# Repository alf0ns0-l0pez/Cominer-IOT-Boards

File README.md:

# Cominer-IOT-Boards
Cominer IOT Boards - IOT Multiple Actions

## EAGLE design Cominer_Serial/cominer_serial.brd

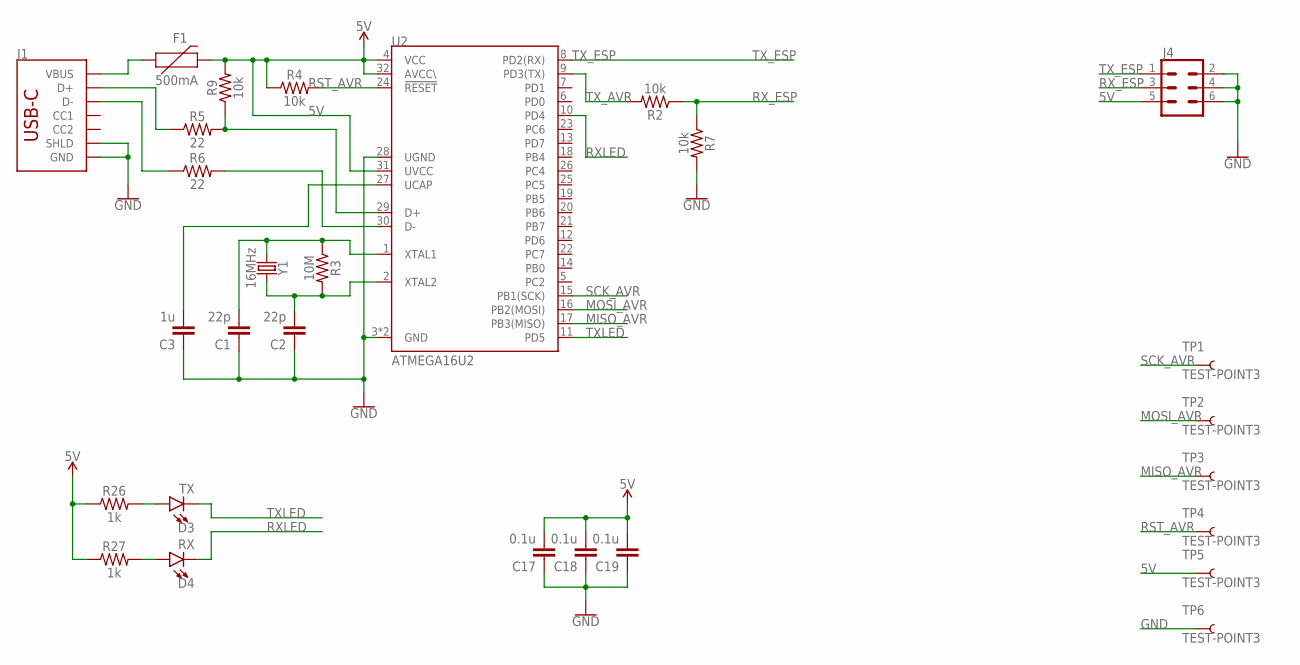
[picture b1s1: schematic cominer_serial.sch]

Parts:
C1, C2: 22p; 0805
C3: 1u; 0805
C17, C18, C19: 0.1u; 0805
D3: TX; LED-0603
D4: RX; LED-0603
F1: 500mA; 1812
J1: USB_C; USB-C-16P-SMD
J4: CONN_03X2SHROUD; 2X3-SHROUDED
R2, R4, R7, R9: 10k; 0805
R3: 10M; 0805
R5, R6: 22; 0805
R26, R27: 1k; 0805
TP1, TP2, TP3, TP4, TP5, TP6: TEST-POINT3; PAD.03X.03
U2: ATMEGA16U2; QFN32
Y1: 16MHz; CRYSTAL-SMD-5X3.2-4PAD

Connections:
5V: C17.2, C18.2, C19.2, F1.2, J4.5, R4.1, R9.2, R26.1, R27.1, TP5.P$1, U2.4 (VCC), U2.31 (UVCC), U2.32 (AVCC\)
GND: C1.1, C2.1, C3.1, C17.1, C18.1, C19.1, J1.GND, J1.GND2 (GND), J1.SHLD1 (SHLD), J1.SHLD2 (SHLD), J1.SHLD3 (SHLD), J1.SHLD4 (SHLD), J4.2, J4.4, J4.6, R7.2, TP6.P$1, U2.3 (GND), U2.28 (UGND), U2.EP (GND)
MISO_AVR: TP3.P$1, U2.17 (PB3(MISO))
MOSI_AVR: TP2.P$1, U2.16 (PB2(MOSI))
unnamed: C1.2, R3.1, U2.1 (XTAL1), Y1.1
unnamed: C2.2, R3.2, U2.2 (XTAL2), Y1.3 (2)
unnamed: C3.2, U2.27 (UCAP)
unnamed: R6.2, U2.30 (D-)
unnamed: R5.2, R9.1, U2.29 (D+)
unnamed: J1.A6 (D+), J1.B6 (D+), R5.1
unnamed: J1.A7 (D-), J1.B7 (D-), R6.1
unnamed: F1.1, J1.VBUS1 (VBUS), J1.VBUS2 (VBUS)
unnamed: D3.A, R26.2
unnamed: D4.A, R27.2
RST_AVR: R4.2, TP4.P$1, U2.24 (!RESET)
RXLED: D4.C, U2.10 (PD4)
RX_ESP: J4.3, R2.1, R7.1
SCK_AVR: TP1.P$1, U2.15 (PB1(SCK))
TXLED: D3.C, U2.11 (PD5)
TX_AVR: R2.2, U2.9 (PD3(TX))
TX_ESP: J4.1, U2.8 (PD2(RX))

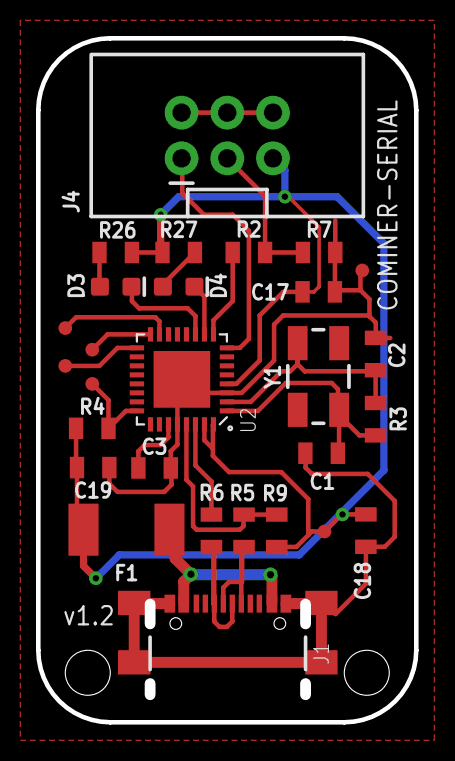
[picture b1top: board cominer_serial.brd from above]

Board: 2 copper layers, 20.7 x 37.7 mm, 28 parts (0 on the bottom side), 21 nets.

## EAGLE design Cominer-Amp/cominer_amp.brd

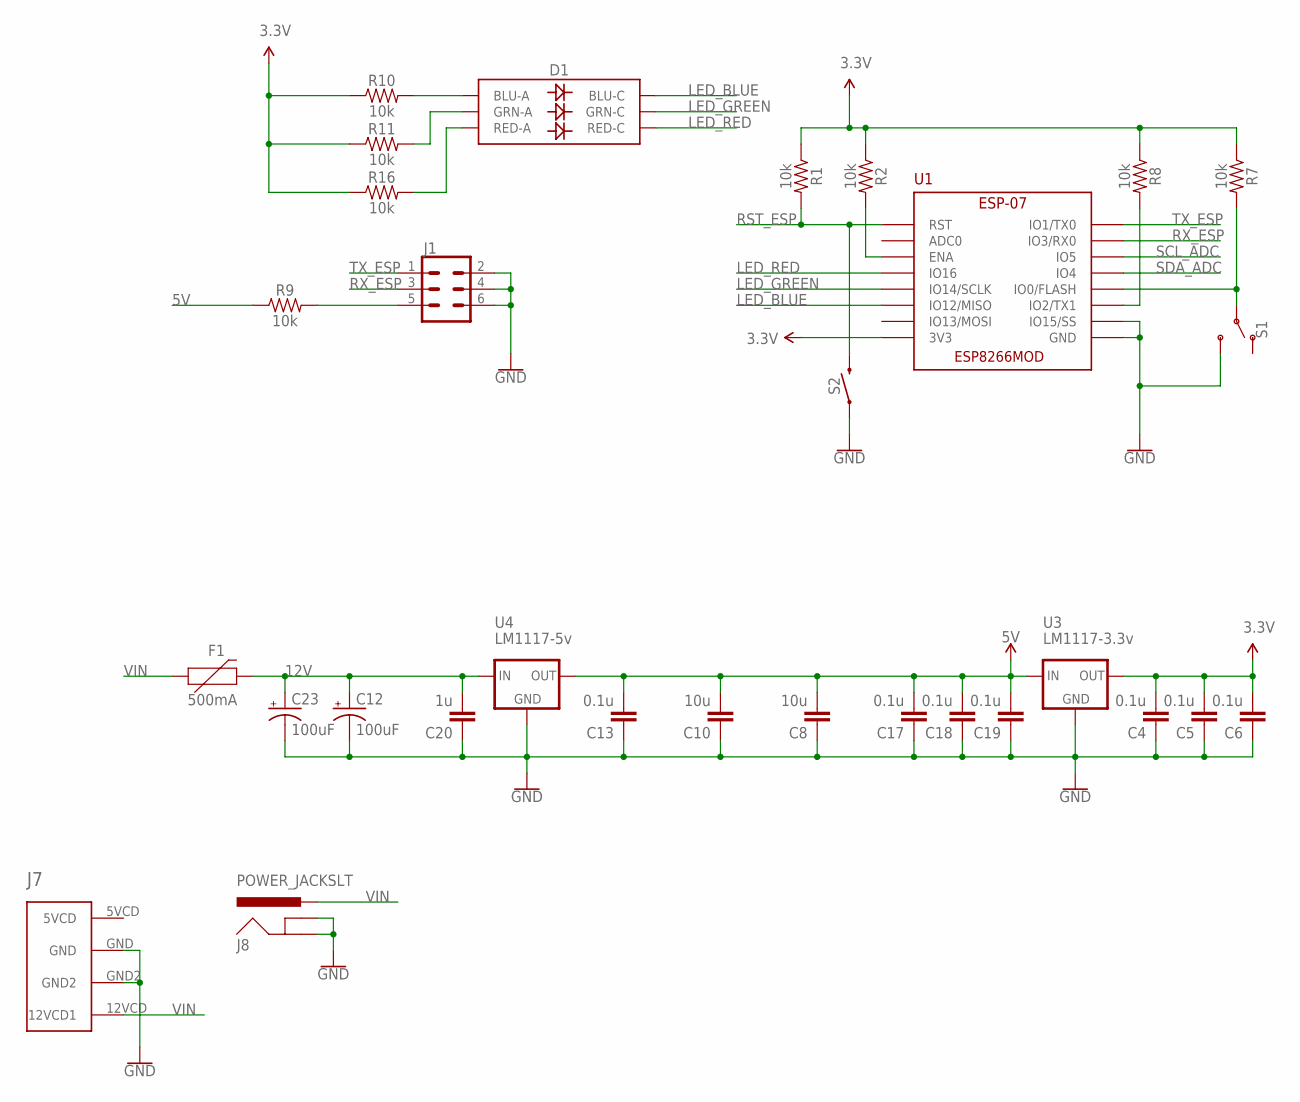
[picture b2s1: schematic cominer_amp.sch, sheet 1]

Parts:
C4, C5, C6, C13, C17, C18, C19: 0.1u; 0805
C8, C10: 10u; 0805
C12, C23: 100uF; PANASONIC_D
C20: 1u; 0805
D1: LED-RGBNO_IC; LED-TRICOLOR-5050
F1: 500mA; 1812
J1: CONN_03X2SHROUD; 2X3-SHROUDED
J7: MOLEX-CPU-POWER; MOLEX-5.08-4PIN
J8: POWER_JACKSLT; POWER_JACK_SLOT
R1, R2, R7, R8, R9, R10, R11, R16: 10k; 0805
S1: SWITCH-SPDT-SMD-RIGHT-ANGLE; SWITCH_SPST_SMD_A
S2: MOMENTARY-SWITCH-SPST-SMD-6.0X3.5MM; TACTILE_SWITCH_SMD_6.0X3.5MM
U1: ESP-07
U3: LM1117-3.3v; SOT223
U4: LM1117-5v; SOT223

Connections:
3.3V: C4.2, C5.2, C6.2, R1.1, R2.1, R7.1, R8.1, R10.1, R11.1, R16.1, U1.3V3, U3.2 (OUT); also elsewhere on the board
5V: C8.2, C10.2, C13.2, C17.2, C18.2, C19.2, R9.1, U3.3 (IN), U4.2 (OUT); also elsewhere on the board
12V: C12.+, C20.2, C23.+, F1.2, U4.3 (IN)
GND: C4.1, C5.1, C6.1, C8.1, C10.1, C12.-, C13.1, C17.1, C18.1, C19.1, C20.1, C23.-, J1.2, J1.4, J1.6, J7.GND, J7.GND2, J8.GND@1 (GNDBREAK), J8.GND@2 (GND), S1.3 (S), S2.1, U1.GND, U1.IO15 (IO15/SS), U3.1 (GND), U4.1 (GND); also elsewhere on the board
LED_BLUE: D1.4 (BLU-C), U1.IO12 (IO12/MISO)
LED_GREEN: D1.6 (GRN-C), U1.IO14 (IO14/SCLK)
LED_RED: D1.5 (RED-C), U1.I016 (IO16)
unnamed: R7.2, S1.2, U1.IO0 (IO0/FLASH)
unnamed: R8.2, U1.IO2 (IO2/TX1)
unnamed: J1.5, R9.2
unnamed: D1.3 (BLU-A), R10.2
unnamed: D1.1 (GRN-A), R11.2
unnamed: D1.2 (RED-A), R16.2
unnamed: R2.2, U1.ENA
RST_ESP: R1.2, S2.2, U1.RST
RX_ESP: J1.3, U1.RX0 (IO3/RX0)
SCL_ADC: U1.IO5; also elsewhere on the board
SDA_ADC: U1.IO4; also elsewhere on the board
TX_ESP: J1.1, U1.TX0 (IO1/TX0)
VIN: F1.1, J7.12VCD (12VCD1), J8.PWR

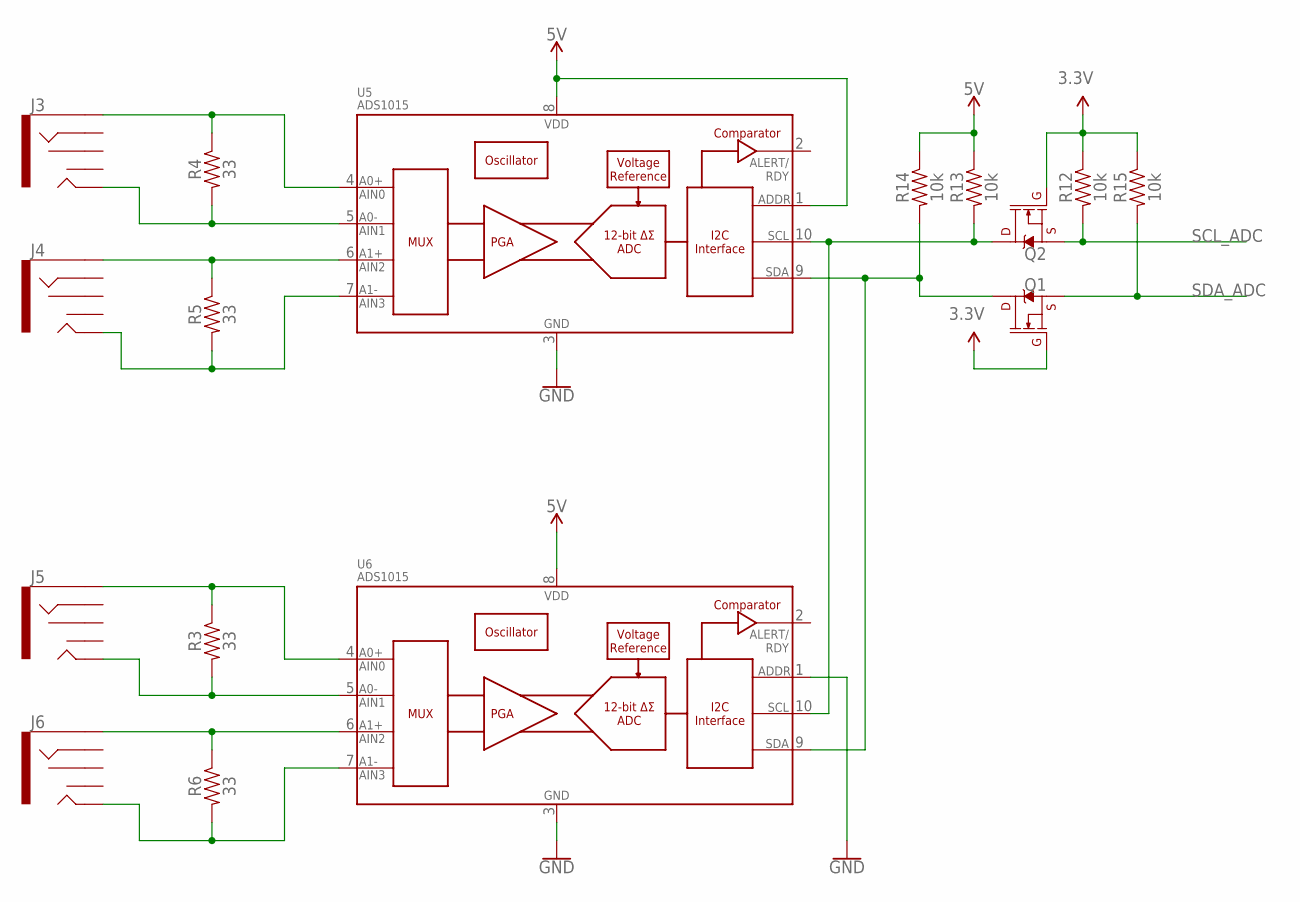
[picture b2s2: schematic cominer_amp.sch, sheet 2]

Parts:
J3, J4, J5, J6: AUDIO_JACK_3.5MM_PTH; AUDIO-JACK
Q1, Q2: BSS138; SOT23-3
R3, R4, R5, R6: 33; 0805
R12, R13, R14, R15: 10k; 0805
U5, U6: ADS1015; MSOP10

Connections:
3.3V: Q1.1 (G), Q2.1 (G), R12.1, R15.1; also elsewhere on the board
5V: R13.1, R14.1, U5.1 (ADDR), U5.8 (VDD), U6.8 (VDD); also elsewhere on the board
GND: U5.3 (VSS), U6.1 (ADDR), U6.3 (VSS); also elsewhere on the board
unnamed: J4.TIP, R5.2, U5.7 (AIN3)
unnamed: J3.SLEEVE, R4.1, U5.4 (AIN0)
unnamed: J3.TIP, R4.2, U5.5 (AIN1)
unnamed: J4.SLEEVE, R5.1, U5.6 (AIN2)
unnamed: J5.TIP, R3.2, U6.5 (AIN1)
unnamed: Q1.3 (D), R14.2, U5.9 (SDA), U6.9 (SDA)
unnamed: J5.SLEEVE, R3.1, U6.4 (AIN0)
unnamed: Q2.3 (D), R13.2, U5.10 (SCL), U6.10 (SCL)
unnamed: J6.TIP, R6.2, U6.7 (AIN3)
unnamed: J6.SLEEVE, R6.1, U6.6 (AIN2)
SCL_ADC: Q2.2 (S), R12.2; also elsewhere on the board
SDA_ADC: Q1.2 (S), R15.2; also elsewhere on the board

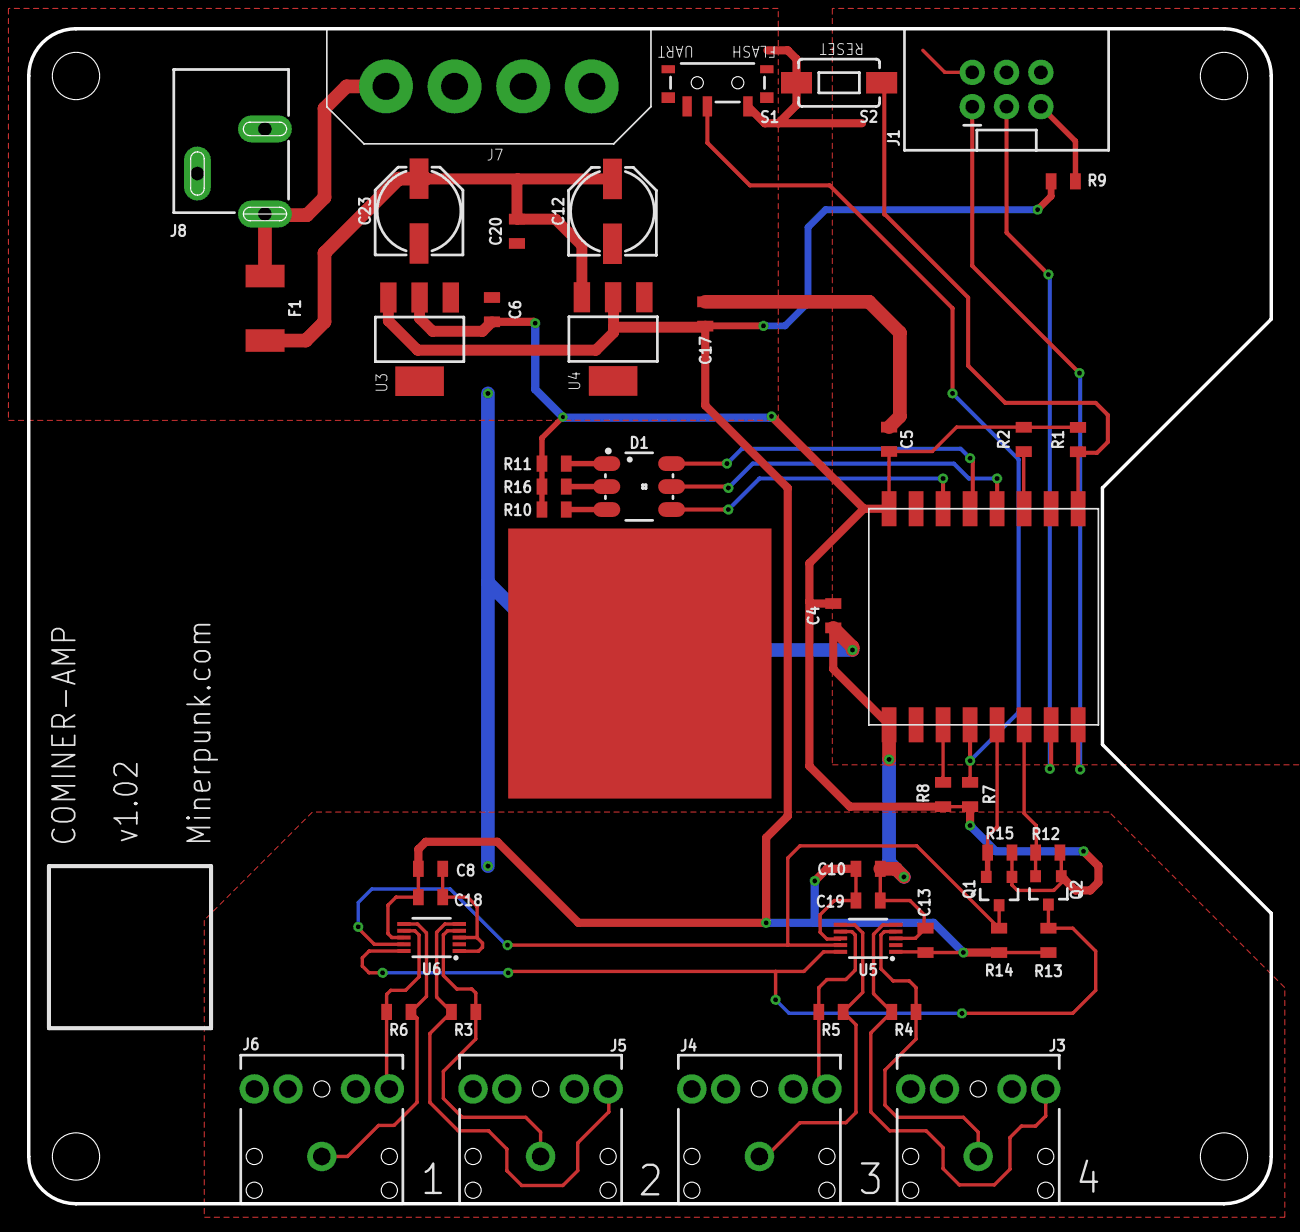
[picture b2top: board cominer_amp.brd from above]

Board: 2 copper layers, 92.0 x 87.0 mm, 46 parts (0 on the bottom side), 30 nets.

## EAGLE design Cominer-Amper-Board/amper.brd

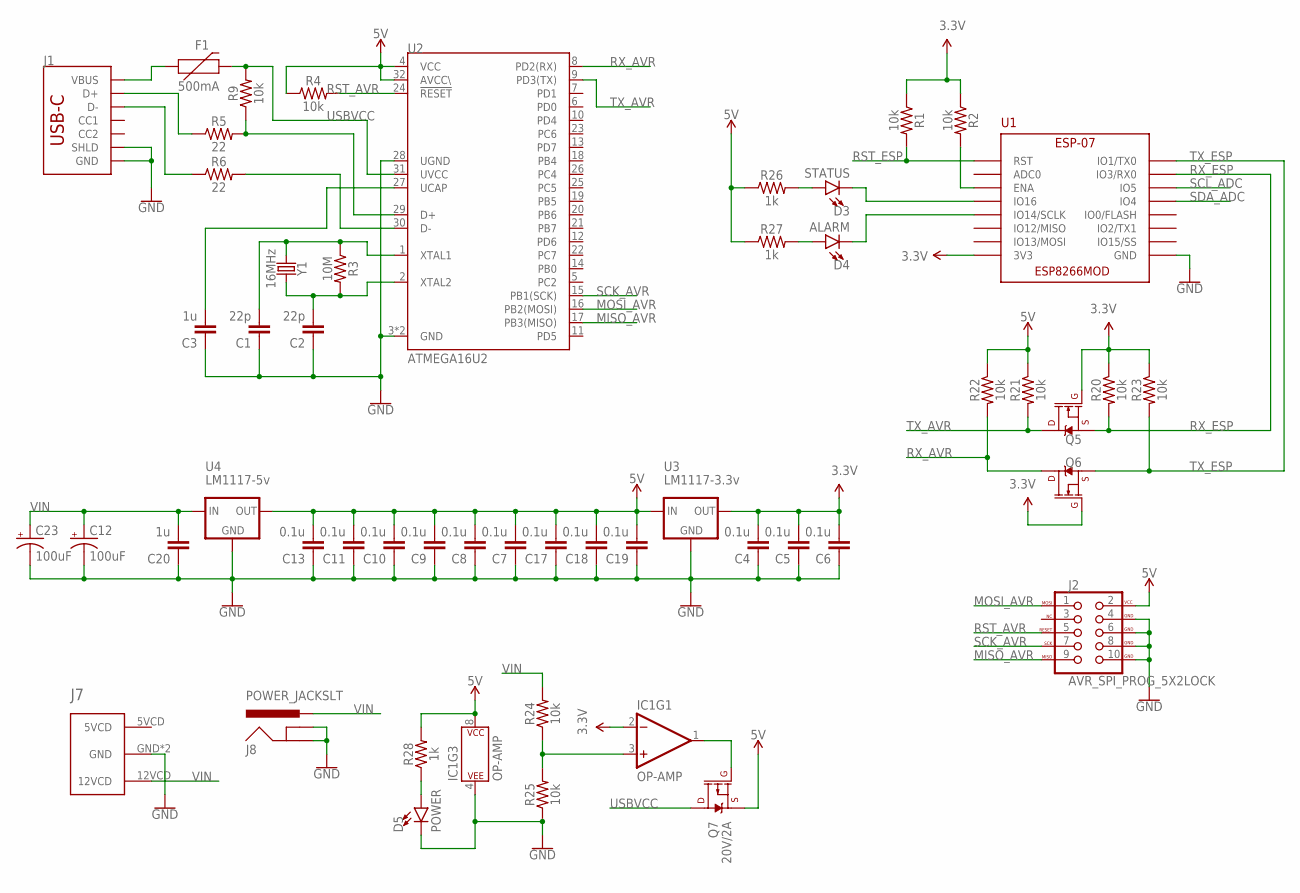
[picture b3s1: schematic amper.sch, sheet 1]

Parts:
C1, C2: 22p; 0805
C3, C20: 1u; 0805
C4, C5, C6, C7, C8, C9, C10, C11, C13, C17, C18, C19: 0.1u; 0805
C12, C23: 100uF; PANASONIC_D
D3: STATUS; LED-0603
D4: ALARM; LED-0603
D5: POWER; LED-0603
F1: 500mA; 1812
IC1: OP-AMP; SO08
J1: USB_C_2-LAYER_PADS; USB-C-16P-2LAYER-PADS
J2: AVR_SPI_PROG_5X2LOCK; 2X5-SHROUDED_LOCK
J7: MOLEX-CPU-POWER; MOLEX-5.08-4PIN
J8: POWER_JACKSLT; POWER_JACK_SLOT
Q5, Q6: 220mA/50V/3.5Ω; SOT23-3
Q7: 20V/2A; SOT23-3
R1, R2, R4, R9, R20, R21, R22, R23, R24, R25: 10k; 0805
R3: 10M; 0805
R5, R6: 22; 0805
R26, R27, R28: 1k; 0805
U1: ESP-07
U2: ATMEGA16U2; QFN32
U3: LM1117-3.3v; SOT223
U4: LM1117-5v; SOT223
Y1: 16MHz; CRYSTAL-SMD-5X3.2-4PAD

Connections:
3.3V: C4.2, C5.2, C6.2, IC1.2 (-IN), Q5.1 (G), Q6.1 (G), R1.1, R2.1, R20.1, R23.1, U1.3V3, U3.2 (OUT); also elsewhere on the board
5V: C7.2, C8.2, C9.2, C10.2, C11.2, C13.2, C17.2, C18.2, C19.2, IC1.8 (P$V+), J2.2 (VCC), Q7.2 (S), R4.1, R21.1, R22.1, R26.1, R27.1, R28.2, U2.4 (VCC), U2.32 (AVCC\), U3.3 (IN), U4.2 (OUT); also elsewhere on the board
GND: C1.1, C2.1, C3.1, C4.1, C5.1, C6.1, C7.1, C8.1, C9.1, C10.1, C11.1, C12.-, C13.1, C17.1, C18.1, C19.1, C20.1, C23.-, D5.C, IC1.4 (P$V-), J1.GND, J1.GND2 (GND), J1.SHLD1 (SHLD), J1.SHLD2 (SHLD), J1.SHLD3 (SHLD), J1.SHLD4 (SHLD), J2.4 (GND), J2.6 (GND), J2.8 (GND), J2.10 (GND), J7.GND, J7.GND2 (GND), J8.GND@1 (GNDBREAK), J8.GND@2 (GND), R25.1, U1.GND, U2.3 (GND), U2.28 (UGND), U2.EP (GND), U3.1 (GND), U4.1 (GND); also elsewhere on the board
MISO_AVR: J2.9 (MISO), U2.17 (PB3(MISO))
MOSI_AVR: J2.1 (MOSI), U2.16 (PB2(MOSI))
unnamed: C1.2, R3.1, U2.1 (XTAL1), Y1.1
unnamed: C2.2, R3.2, U2.2 (XTAL2), Y1.3 (2)
unnamed: C3.2, U2.27 (UCAP)
unnamed: R6.2, U2.30 (D-)
unnamed: R5.2, R9.1, U2.29 (D+)
unnamed: J1.A6 (D+), J1.B6 (D+), R5.1
unnamed: J1.A7 (D-), J1.B7 (D-), R6.1
unnamed: F1.1, J1.VBUS1 (VBUS), J1.VBUS2 (VBUS)
unnamed: R2.2, U1.ENA
unnamed: IC1.1 (OUT), Q7.1 (G)
unnamed: IC1.3 (+IN), R24.1, R25.2
unnamed: D3.C, U1.I016 (IO16)
unnamed: D4.C, U1.IO14 (IO14/SCLK)
unnamed: D3.A, R26.2
unnamed: D4.A, R27.2
unnamed: D5.A, R28.1
RST_AVR: J2.5 (RESET), R4.2, U2.24 (!RESET)
RST_ESP: R1.2, U1.RST
RX_AVR: Q6.3 (D), R22.2, U2.8 (PD2(RX))
RX_ESP: Q5.2 (S), R20.2, U1.RX0 (IO3/RX0)
SCK_AVR: J2.7 (SCK), U2.15 (PB1(SCK))
SCL_ADC: U1.IO5; also elsewhere on the board
SDA_ADC: U1.IO4; also elsewhere on the board
TX_AVR: Q5.3 (D), R21.2, U2.9 (PD3(TX))
TX_ESP: Q6.2 (S), R23.2, U1.TX0 (IO1/TX0)
USBVCC: F1.2, Q7.3 (D), R9.2, U2.31 (UVCC)
VIN: C12.+, C20.2, C23.+, J7.12VCD, J8.PWR, R24.2, U4.3 (IN)

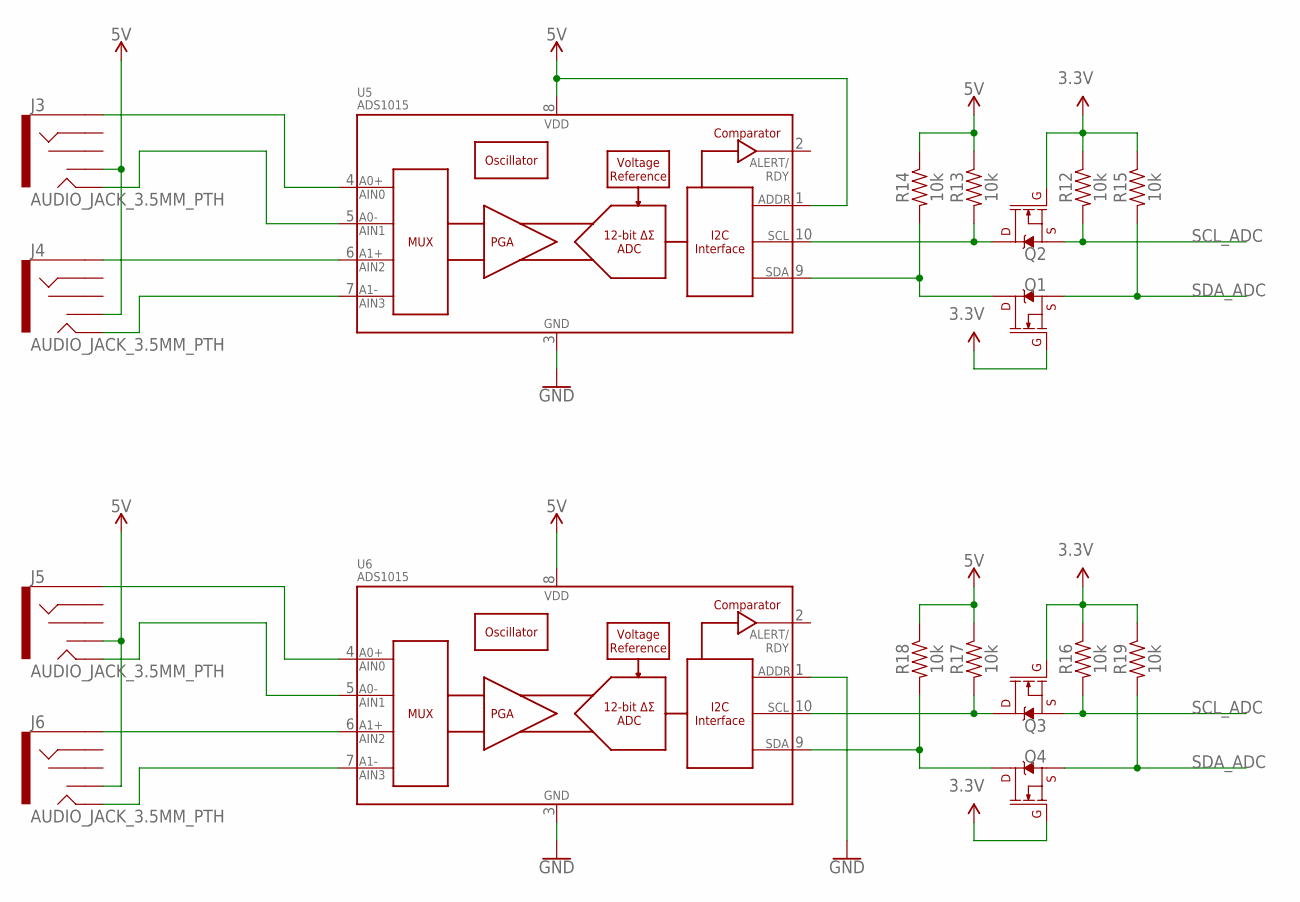
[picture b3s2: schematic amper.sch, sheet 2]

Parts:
J3, J4, J5, J6: AUDIO_JACK_3.5MM_PTH; AUDIO-JACK
Q1, Q2, Q3, Q4: 220mA/50V/3.5Ω; SOT23-3
R12, R13, R14, R15, R16, R17, R18, R19: 10k; 0805
U5, U6: ADS1015; MSOP10

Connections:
3.3V: Q1.1 (G), Q2.1 (G), Q3.1 (G), Q4.1 (G), R12.1, R15.1, R16.1, R19.1; also elsewhere on the board
5V: J3.TSH, J4.TSH, J5.TSH, J6.TSH, R13.1, R14.1, R17.1, R18.1, U5.1 (ADDR), U5.8 (VDD), U6.8 (VDD); also elsewhere on the board
GND: U5.3 (VSS), U6.1 (ADDR), U6.3 (VSS); also elsewhere on the board
unnamed: J3.SLEEVE, U5.4 (AIN0)
unnamed: J3.TIP, U5.5 (AIN1)
unnamed: J4.TIP, U5.7 (AIN3)
unnamed: J4.SLEEVE, U5.6 (AIN2)
unnamed: J5.TIP, U6.5 (AIN1)
unnamed: Q1.3 (D), R14.2, U5.9 (SDA)
unnamed: J5.SLEEVE, U6.4 (AIN0)
unnamed: Q2.3 (D), R13.2, U5.10 (SCL)
unnamed: J6.TIP, U6.7 (AIN3)
unnamed: J6.SLEEVE, U6.6 (AIN2)
unnamed: Q3.3 (D), R17.2, U6.10 (SCL)
unnamed: Q4.3 (D), R18.2, U6.9 (SDA)
SCL_ADC: Q2.2 (S), Q3.2 (S), R12.2, R16.2; also elsewhere on the board
SDA_ADC: Q1.2 (S), Q4.2 (S), R15.2, R19.2; also elsewhere on the board

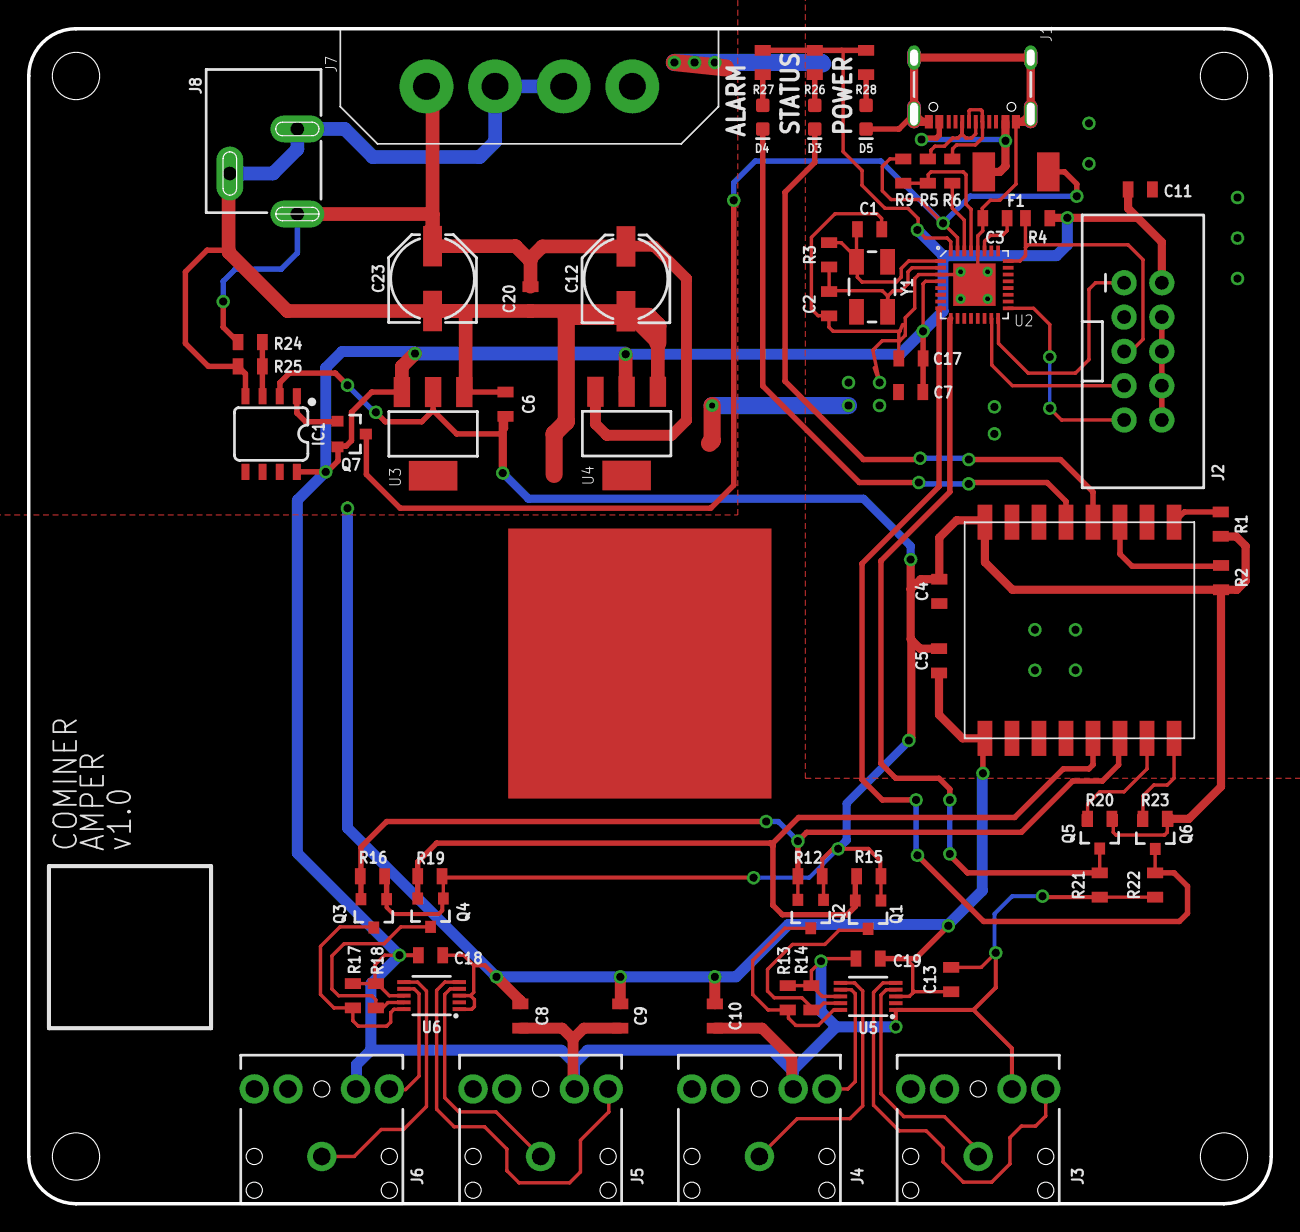
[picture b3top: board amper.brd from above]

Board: 2 copper layers, 91.7 x 86.7 mm, 69 parts (0 on the bottom side), 44 nets.

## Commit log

2022-02-14 Add board base idea
2022-02-18 add usb to serialport circuit and lm1117 regulator
2022-02-22 all devices were order
2022-02-23 cominer-amp board complete
2022-03-16 amper board is ready
2022-04-20 add serial and amp board

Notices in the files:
parts and their libraries:
SparkFun-Resistors: Licensing: Creative Commons ShareAlike 4.0 International - https://creativecommons.org/licenses/by-sa/4.0
